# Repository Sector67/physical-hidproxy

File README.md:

A Physical HID proxy
====================

So we have an Android phone running some security-sensitive software, as a prototype.
Part of the software is that is has to "pretend" to be a keyboard on a computer.
An Android phone can't do this without the kernel being recompiled.
This project gets around that limitation by using a USB=>FTDI cable connected to
an Arduino running V-USB HID, which sets itself up as a keyboard.
Every SerialEvent, V-USB's keypress command is called.
Thus, every character over serial ends up being typed, which is a hack, but works ;)

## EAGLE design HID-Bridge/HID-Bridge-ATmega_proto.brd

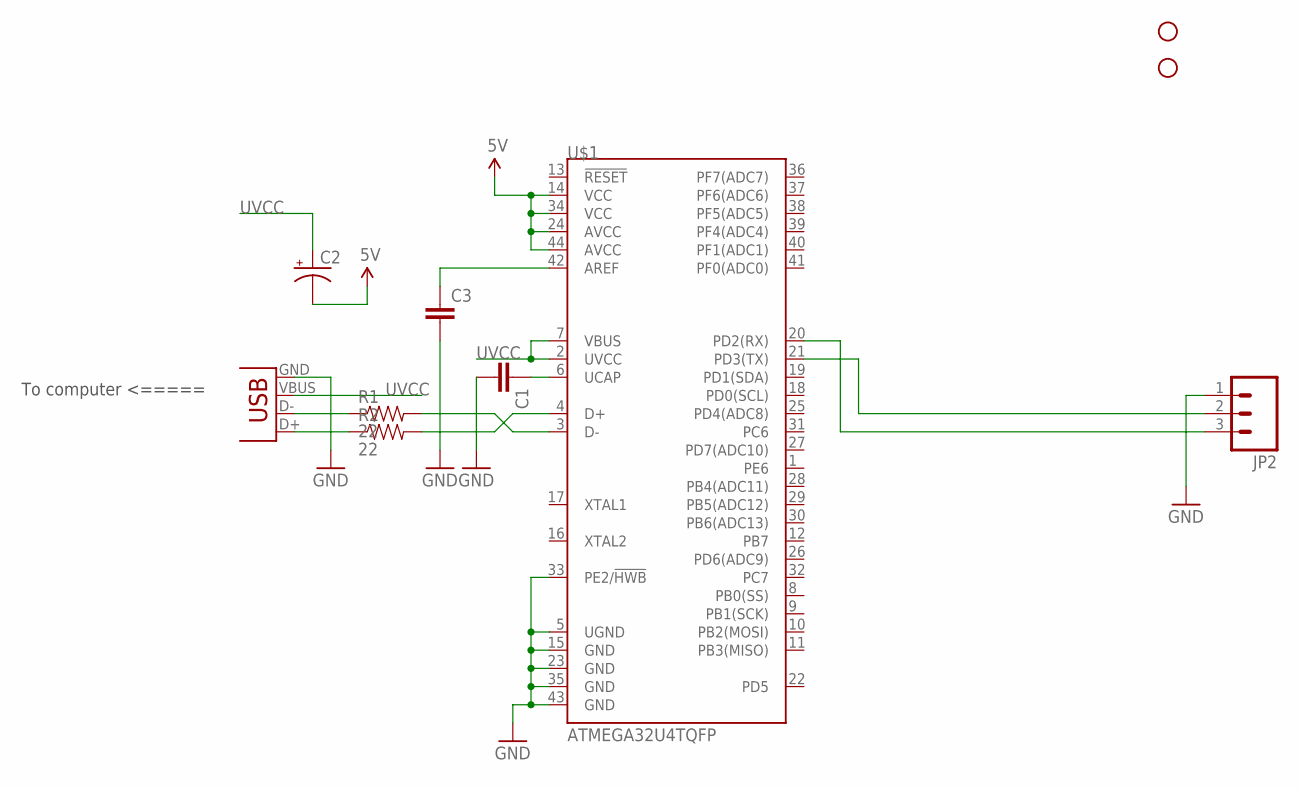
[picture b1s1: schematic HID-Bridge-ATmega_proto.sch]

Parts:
C1, C3: CAPPTH; CAP-PTH-SMALL
C2: 10UF-25V-20%(PTH); CPOL-RADIAL-10UF-25V
JP1: USB-B; USB-B-PTH
JP2: M03PTH; 1X03
R1, R2: 22; AXIAL-0.1
STANDOFF1, STANDOFF2: STAND-OFF
U$1: ATMEGA32U4TQFP; SPARKFUN-DIGITALIC_TQFP44

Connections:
5V: C2.2 (-), U$1.14 (VCC), U$1.24 (AVCC), U$1.34 (VCC), U$1.44 (AVCC)
GND: C1.2, C3.2, JP1.GND, JP2.1, U$1.5 (UGND), U$1.15 (GND), U$1.23 (GND), U$1.33 (PE2/!HWB), U$1.35 (GND), U$1.43 (GND)
unnamed: JP1.D-, R1.P$1 (1)
unnamed: JP1.D+, R2.P$1 (1)
unnamed: R1.P$2 (2), U$1.3 (D-)
unnamed: R2.P$2 (2), U$1.4 (D+)
unnamed: C1.1, U$1.6 (UCAP)
unnamed: C3.1, U$1.42 (AREF)
unnamed: JP2.3, U$1.20 (PD2(RX))
unnamed: JP2.2, U$1.21 (PD3(TX))
UVCC: C2.1 (+), JP1.VBUS, U$1.2 (UVCC), U$1.7 (VBUS)

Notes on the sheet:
To computer <=====

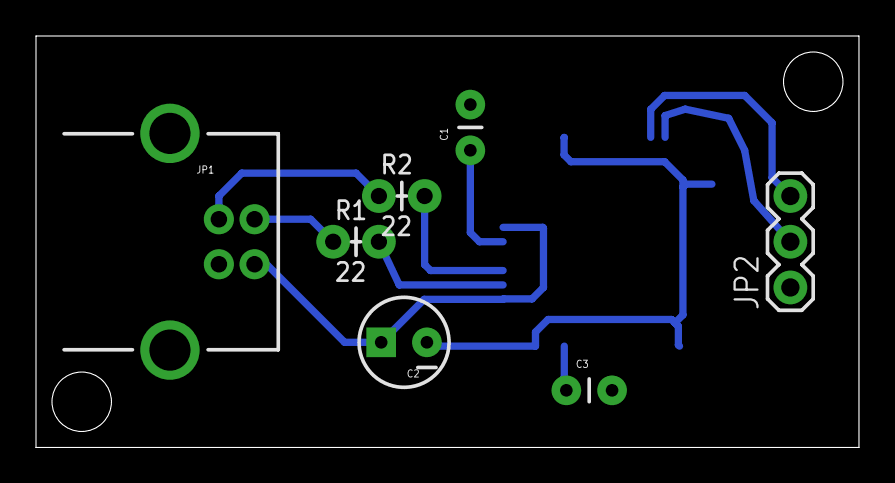
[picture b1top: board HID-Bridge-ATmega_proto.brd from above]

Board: 2 copper layers, 45.7 x 22.9 mm, 10 parts (1 on the bottom side), 11 nets.

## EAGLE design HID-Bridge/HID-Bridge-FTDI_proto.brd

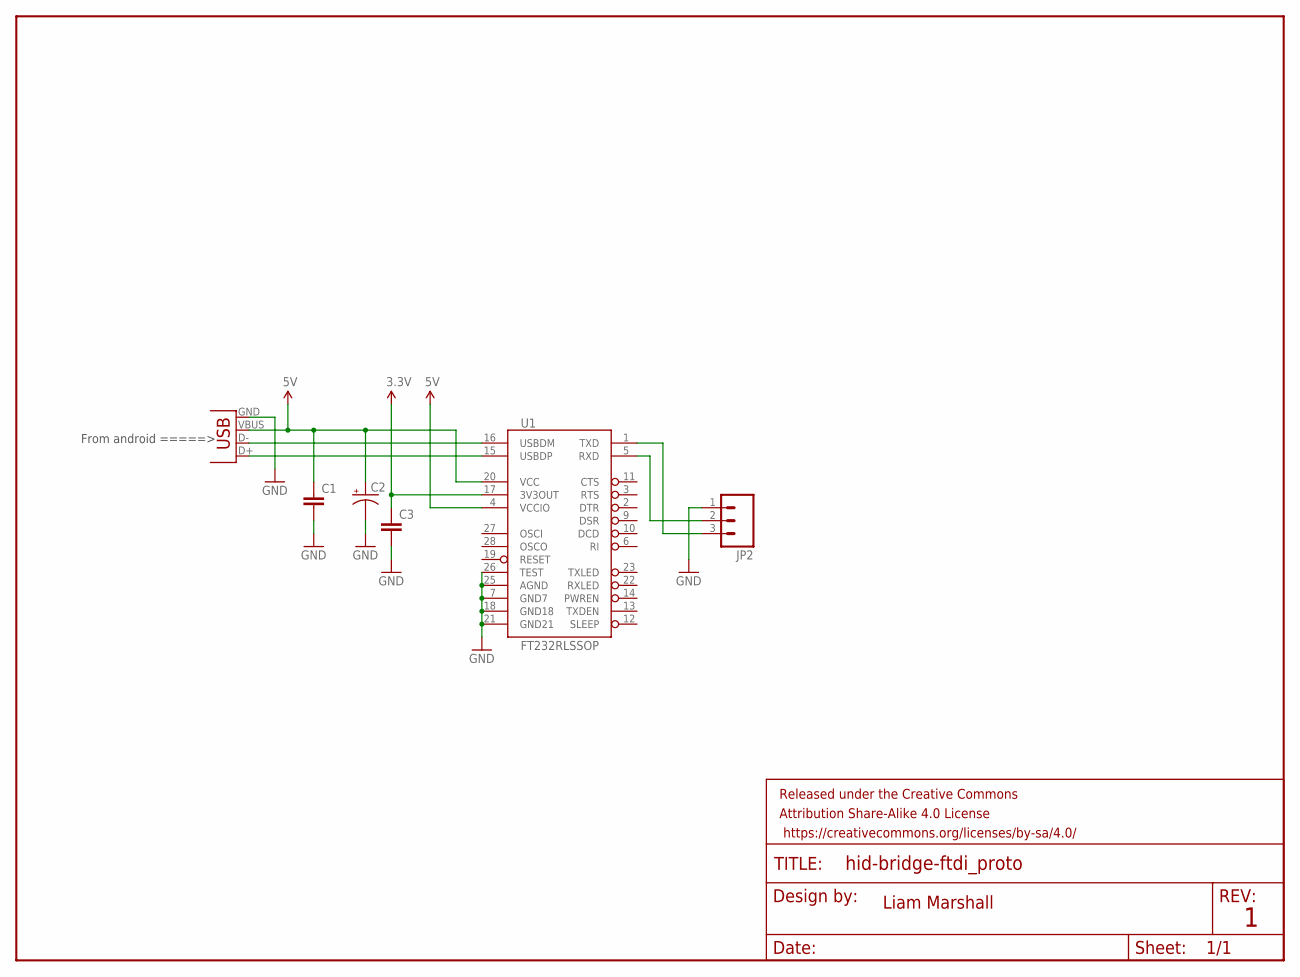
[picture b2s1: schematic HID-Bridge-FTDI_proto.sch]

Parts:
C1, C3: 0.1UF-50V-20%(PTH)KIT-EZ; CAP-PTH-SMALL-KIT
C2: 10UF-25V-20%(PTH); CPOL-RADIAL-10UF-25V
FRAME1: FRAME-LETTER; CREATIVE_COMMONS
JP1: USB-B; USB-B-PTH
JP2: M03PTH; 1X03
U1: FT232RLSSOP; SSOP28DB

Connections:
3.3V: C3.1, U1.17 (3V3OUT)
5V: C1.1, C2.1 (+), JP1.VBUS, U1.4 (VCCIO), U1.20 (VCC)
GND: C1.2, C2.2 (-), C3.2, JP1.GND, JP2.1, U1.7 (GND7), U1.18 (GND18), U1.21 (GND21), U1.25 (AGND), U1.26 (TEST)
unnamed: JP2.2, U1.5 (RXD)
unnamed: JP1.D+, U1.15 (USBDP)
unnamed: JP1.D-, U1.16 (USBDM)
unnamed: JP2.3, U1.1 (TXD)

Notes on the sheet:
From android =====>
Liam Marshall

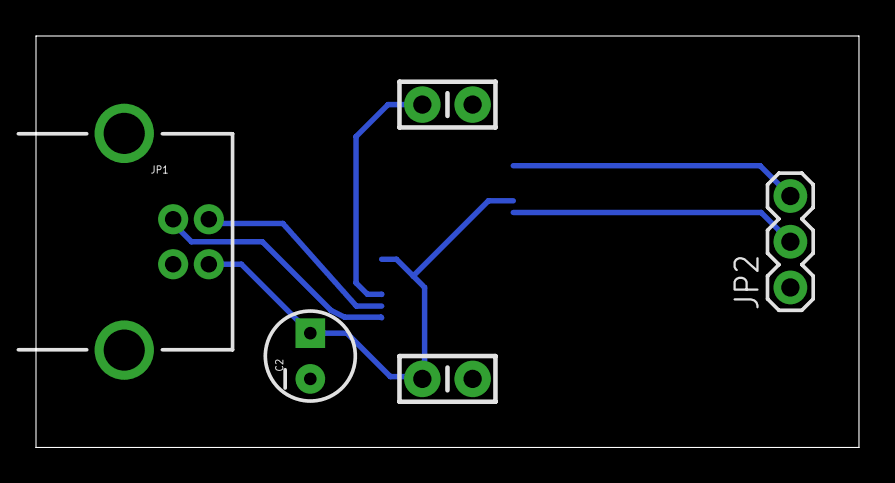
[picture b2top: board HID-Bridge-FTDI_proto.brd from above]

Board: 2 copper layers, 45.7 x 22.9 mm, 7 parts (1 on the bottom side), 7 nets.

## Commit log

2014-09-06 Ino sketch
2014-09-06 explain
2014-09-06 Add libraries
2014-09-06 no arduino right now. get it working first ;)
2014-09-06 Arduino test
2014-09-06 No more of that
2014-09-06 Do it with CDC
2014-09-06 More code
2014-09-07 Basic, (hopefully) working code
2014-09-07 Key test
2014-09-07 It's ALIVE!!!
2014-09-07 Less delay
    Now we can cope with longer messages being sent in one sitting.
2014-09-07 Ramp up the baudrate
    Much better and faster ;)
2014-09-07 Don't need the debug message
2014-09-08 New(er) code
2014-09-08 Faster serial
2014-09-08 Whatever. Slower speed
2014-09-08 Faster again
2014-09-08 More reliable
2014-09-15 Don't need keytest
2014-09-15 Remove USB serial test
2014-09-15 Remove failed V-USB attempt
2014-09-16 Add board files for FTDI -> Serial adaptor (5v, single side)
2014-09-16 Changes for sides etc.
2014-09-16 Ignore *.tap
2014-09-16 Added name
2014-09-18 Changes on FTDI, larger clearance &c
2014-09-18 Initial commit of ATmega board

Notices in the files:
parts and their libraries:
SparkFun-Connectors: Licensing: Creative Commons ShareAlike 4.0 International - https://creativecommons.org/licenses/by-sa/4.0
SparkFun-Aesthetics: Released under the Creative Commons Attribution Share-Alike 4.0 License
SparkFun-Aesthetics: https://creativecommons.org/licenses/by-sa/4.0
